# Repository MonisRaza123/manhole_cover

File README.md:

# MCMS (Manhole Cover Monitoring System)

## Problem Statement
Theft of manhole covers is a severe problem faced by our nation that has been left unaddressed for a long time.The repercussions of this thievery not only amount to material losses but also lead to loss of lives. This project proposes a solution to this problem by building a manhole cover monitoring system. Given that a sensor placed inside the manhole will not have reliable connection to the internet, we can directly send the sensor details using internet. This system will give the real-time status of the covers using a LoRa-based gateway to send the data to a cloud server keeping the authorities informed.

## Introduction and Motivation
Theft of manhole covers leads to accidents and deaths. At
first, this might seem like a very unlikely problem, but in
2004 Calcutta witnessed the theft of more than 10000
manhole covers over a period of two months. Thieves
steal these covers to sell them as scrap iron, the profit
made out of these acts is not much but the loss incurred
by society is much greater.
This type of theft is performed at locations experiencing
less traffic and spots which are not monitored with CCTV
cameras. These uncovered holes pose serious danger to
vehicles, especially two-wheelers which end in fatal crashes.
The pedestrians might be able to spot a big hole in daylight
but at night in darkness the chances of any mishappening
increase manifold.
Thus it becomes imperative to come up with a solution
to curb these acts of petty thievery leading to unfortunate
fatalities.

## Proposed Solution

The suggested model is represented in three sections:

1. **LoRa end-devices:** The end devices are composed of sensors capable of
monitoring the status of the cover on the manhole.
The microcontroller reading this sensor is integrated
with a LoRa transmitter.
1. **Integrating internet connectivity:** Signals from the nodes of a given region would be
received by a common LoRa-based gateway connected
to an internet access point.
1. **Cloud server and web interface:** Using the connectivity provided by the gateway, the
data is uploaded to a cloud-based server and displayed
on a web interface or sent to the municipal authorities.

## Block Diagram Representation
|||
|:--:|:--:|
|*Manhole(End Node)*|*Gateway*|

## Six Box Model
The following is the list of requirements for the proposed solution as per the 'Six box Model' for embedded systems:
- Input sensor to detect the status of the manhole cover.
- Wireless technology for transferring sensor information.
- Cloud server acting as the host and storage for the required data.
- Microcontroller to process and control the node and gateway.
- Power supply for the node and gateway.
- Output devices to access the monitoring of the manhole covers.

|1. INPUT- Flex sensor is used as the input sensor to detect the status of the manhole cover by bending at different angles. The resistance of the sensor changes with change in bending angle thereby facilitating the detection of the presence/absence of the cover.||
|:--|--:|
|2. COMMUNICAITON- LoRa communication is used as the preferred communication technology between the sensor node and the gateway because: i) Internet connectivity is not a viable option for the application. ii) LoRa is ideal for low bandwidth battery operated systems as it consumes minimal power ||
|3. HOST & STORAGE- Blynk IOT serves as the cloud service provider. It stores and hosts the cover status of multiple node devices centrally which can then be fetched remotely from anyplace and anytime.||
|4. POWER SUPPLY- The end nodes are powered by a battery and as such need to be charged periodically.The TP4056 is a complete constant-current/constant-voltage linear charger for single-cell lithium-ion batteries. Its SOP package and low external component count make the TP4056 ideally suited for portable applications. The gateway device is powered by a 5V DC adapter||

|<span style="font-weight:normal">5. MICROCONTROLLERS- ATMEGA168 is the microcontroller of choice for the end node as it consumes very less power and has just the right amount of features to cater to the needs of the end device. ESP32 is used as the microcontroller at the gateway as it requires internet connectivity serving as the internet access point for multiple end nodes. The communication between the end-nodes and gateway is done using Lora transceivers as stated earlier</span>|||
|:--|--|--:|

## Circuit Design

### Schematics
||
|:--:|
|*Schematic for End Node*|

||
|:--:|
|*Schematic for Master Node/Gateway*|

### Board Layouts
||
|:--:|
|*END NODE board layout*|

||
|:--:|
|*MASTER NODE board layout*|

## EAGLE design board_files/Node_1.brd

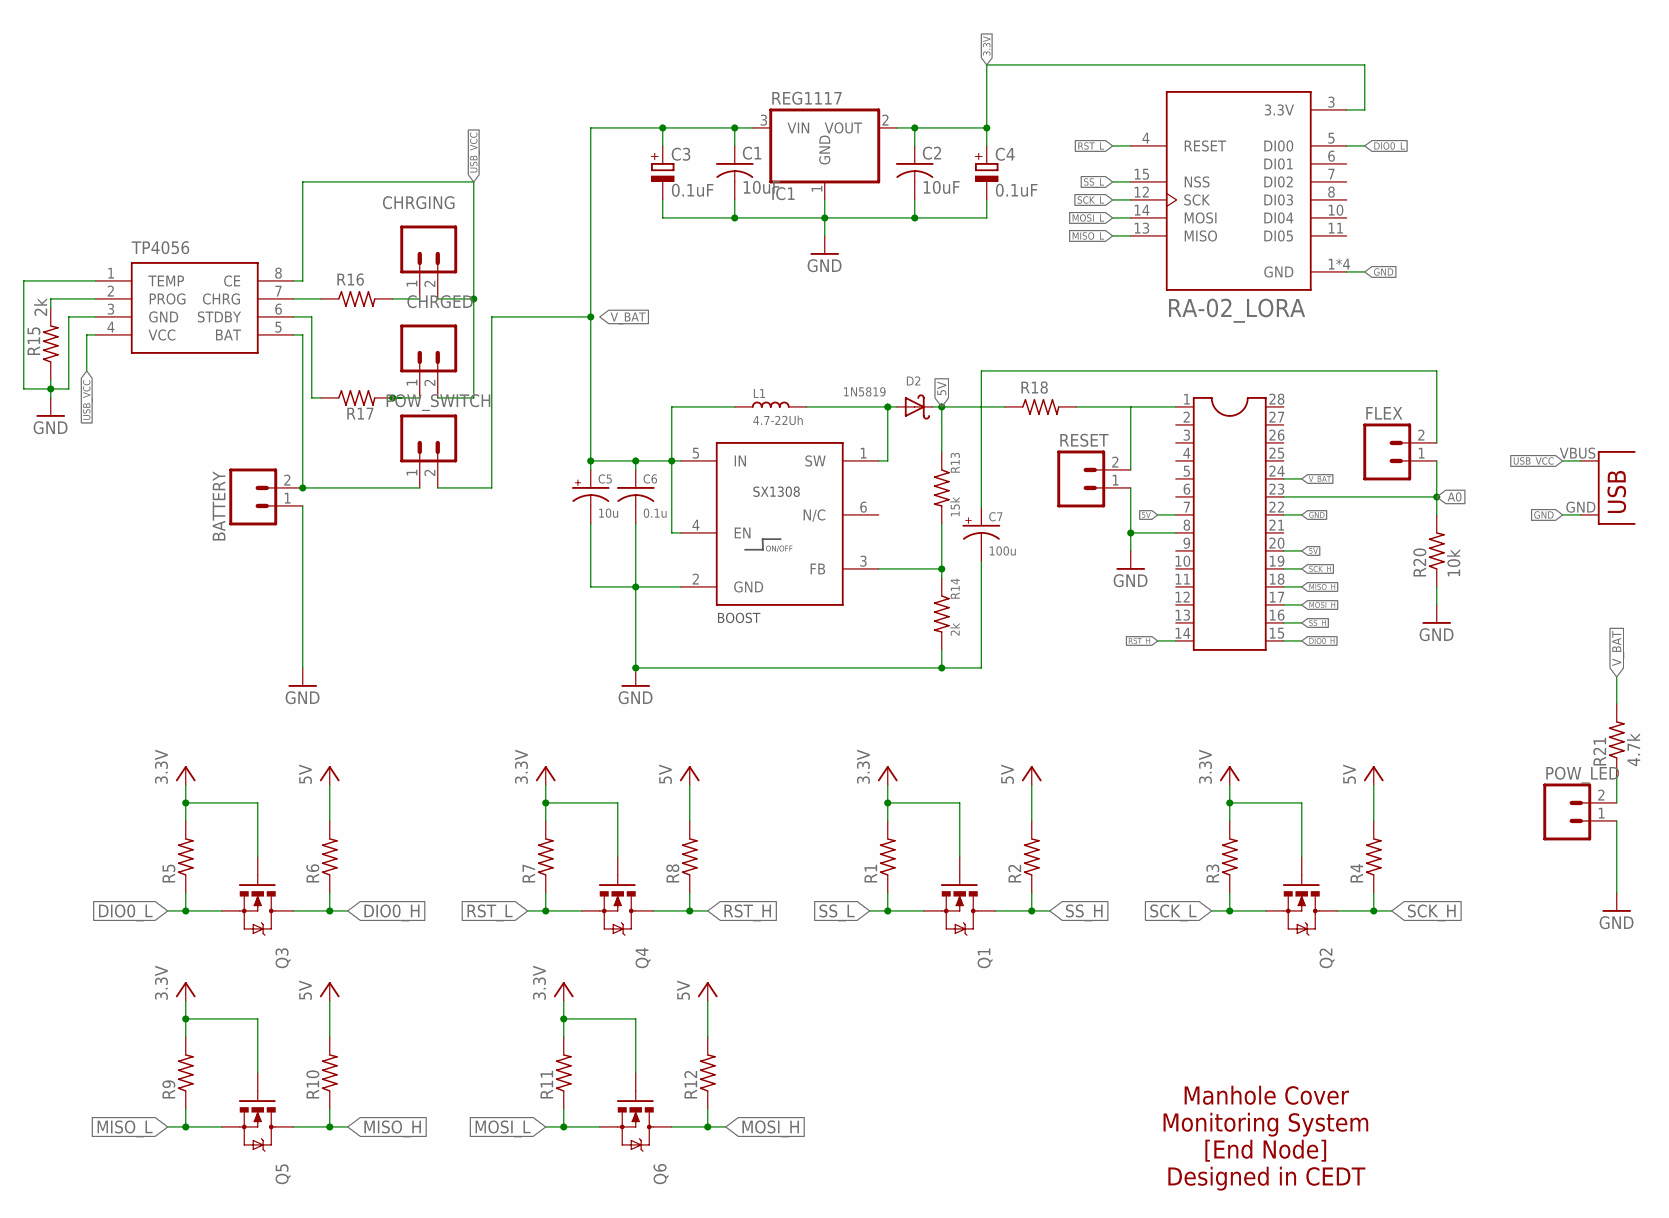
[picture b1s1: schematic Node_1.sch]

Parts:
ATMEGA168: DIL28-3
BATTERY: M02; 02P
BOOST: SX1308; SOT-23-6
C1, C2: 10uF; C0805
C3, C4: 0.1uF; CAPMP3528X210N
C5: 10u; B/3528-21R
C6: 0.1u; C0603
C7: 100u; C/6032-28R
CHRGED: M02; 02P
CHRGING: M02; 02P
D2: 1N5819; DO41-10
FLEX: M02; 02P
IC1: REG1117; SOT223
L1: 4.7-22Uh; INDUCTOR_INT2-3.5-D6.5XH8.0MM
POW_LED: M02; 02P
POW_SWITCH: M02; 02P
Q1, Q2, Q3, Q4, Q5, Q6: MOSFET-NCHANNELBSS138; SOT23
R1, R2, R3, R4, R5, R6, R7, R8, R9, R10, R11, R12: RESISTOR0805; R0805
R13: 15k; M0805
R14: 2k; M0805
R15: 2k; R0805
R16, R17: 470; 0207/7
R18: 10k; 0207/7
R20: 10k; 0207/10
R21: 4.7k; 0207/7
RESET: M02; 02P
TP4056: TP4056; SOP-8
U1: RA-02_LORA; MODULE_RA-02_LORA
U$1: USB(POWER)

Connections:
3.3V: C2.1, C4.1 (+), IC1.2 (VOUT), Q1.1 (G), Q2.1 (G), Q3.1 (G), Q4.1 (G), Q5.1 (G), Q6.1 (G), R1.2, R3.2, R5.2, R7.2, R9.2, R11.2, U1.3 (3.3V)
5V: ATMEGA168.7, ATMEGA168.20, C7.+, D2.C, FLEX.2, R2.2, R4.2, R6.2, R8.2, R10.2, R12.2, R13.1, R18.1
A0: ATMEGA168.23, FLEX.1, R20.2
BAT: BATTERY.2, POW_SWITCH.1, TP4056.5 (BAT)
DIO0_H: ATMEGA168.15, Q3.3 (D), R6.1
DIO0_L: Q3.2 (S), R5.1, U1.5 (DI00)
GND: ATMEGA168.8, ATMEGA168.22, BATTERY.1, BOOST.2 (GND), C1.2, C2.2, C3.2 (-), C4.2 (-), C5.-, C6.2, C7.-, IC1.1 (GND), POW_LED.1, R14.2, R15.1, R20.1, RESET.1, TP4056.1 (TEMP), TP4056.3 (GND), U1.1 (GND), U1.2 (GND), U1.9 (GND), U1.16 (GND), U$1.GND
MISO_H: ATMEGA168.18, Q5.3 (D), R10.1
MISO_L: Q5.2 (S), R9.1, U1.13 (MISO)
MOSI_H: ATMEGA168.17, Q6.3 (D), R12.1
MOSI_L: Q6.2 (S), R11.1, U1.14 (MOSI)
unnamed: BOOST.1 (SW), D2.A, L1.2
unnamed: R15.2, TP4056.2 (PROG)
unnamed: R16.1, TP4056.7 (CHRG)
unnamed: POW_LED.2, R21.1
unnamed: BOOST.3 (FB), R13.2, R14.1
unnamed: R17.1, TP4056.6 (STDBY)
unnamed: CHRGING.1, R16.2
unnamed: ATMEGA168.1, R18.2, RESET.2
unnamed: CHRGED.1, R17.2
RST_H: ATMEGA168.14, Q4.3 (D), R8.1
RST_L: Q4.2 (S), R7.1, U1.4 (RESET)
SCK_H: ATMEGA168.19, Q2.3 (D), R4.1
SCK_L: Q2.2 (S), R3.1, U1.12 (SCK)
SS_H: ATMEGA168.16, Q1.3 (D), R2.1
SS_L: Q1.2 (S), R1.1, U1.15 (NSS)
USB_VCC: CHRGED.2, CHRGING.2, TP4056.4 (VCC), TP4056.8 (CE), U$1.VBUS (VCC)
V_BAT: ATMEGA168.24, BOOST.4 (EN), BOOST.5 (IN), C1.1, C3.1 (+), C5.+, C6.1, IC1.3 (VIN), L1.1, POW_SWITCH.2, R21.2

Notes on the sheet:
Manhole Cover Monitoring System [End Node] Designed in CEDT

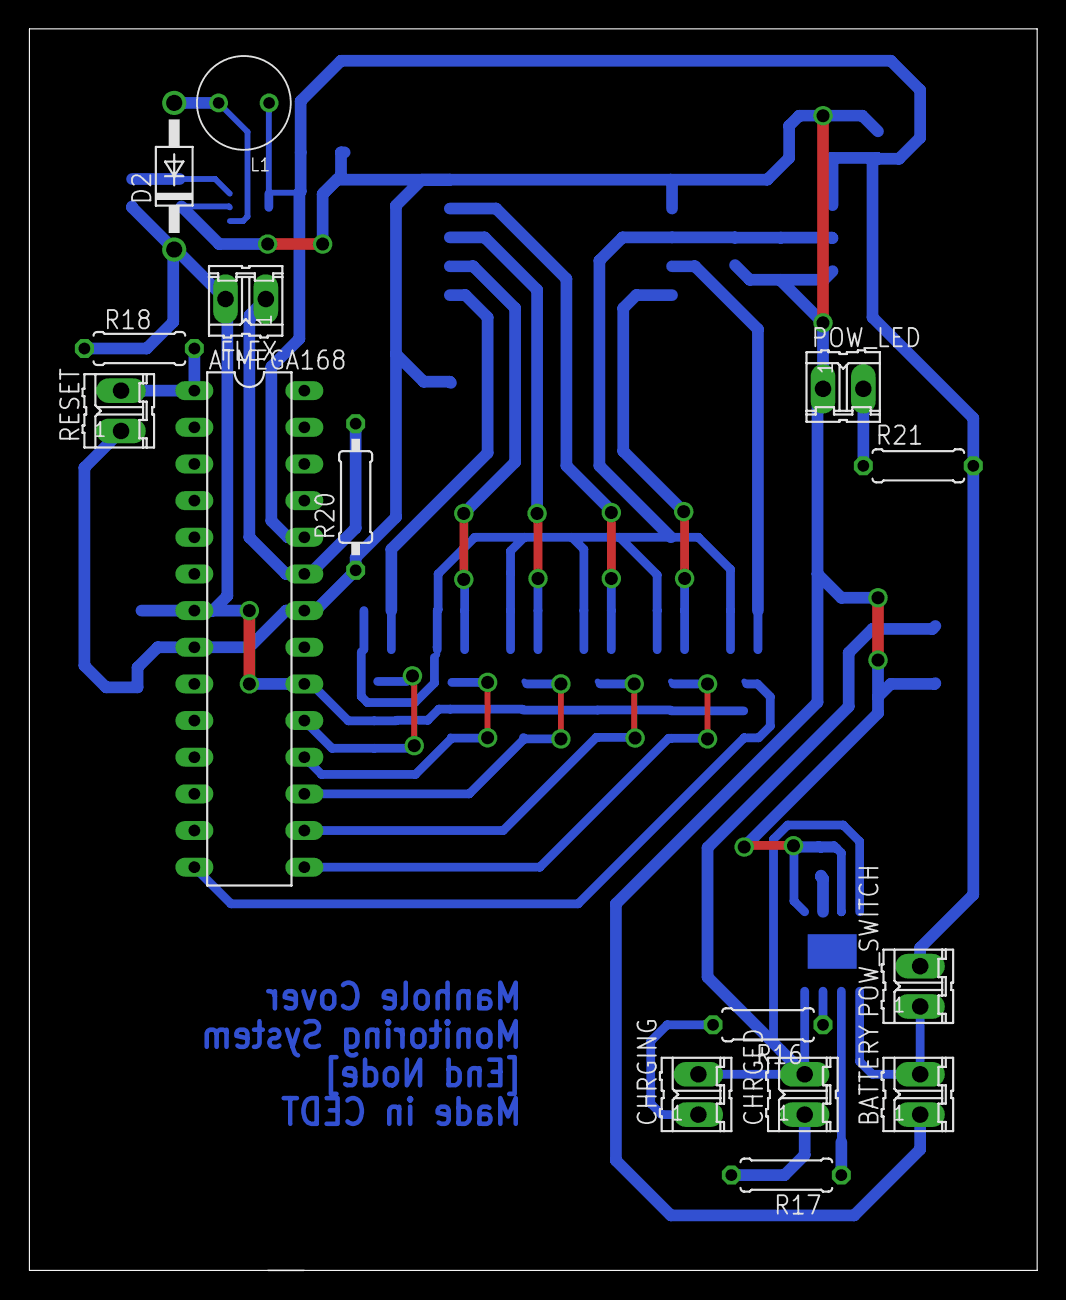
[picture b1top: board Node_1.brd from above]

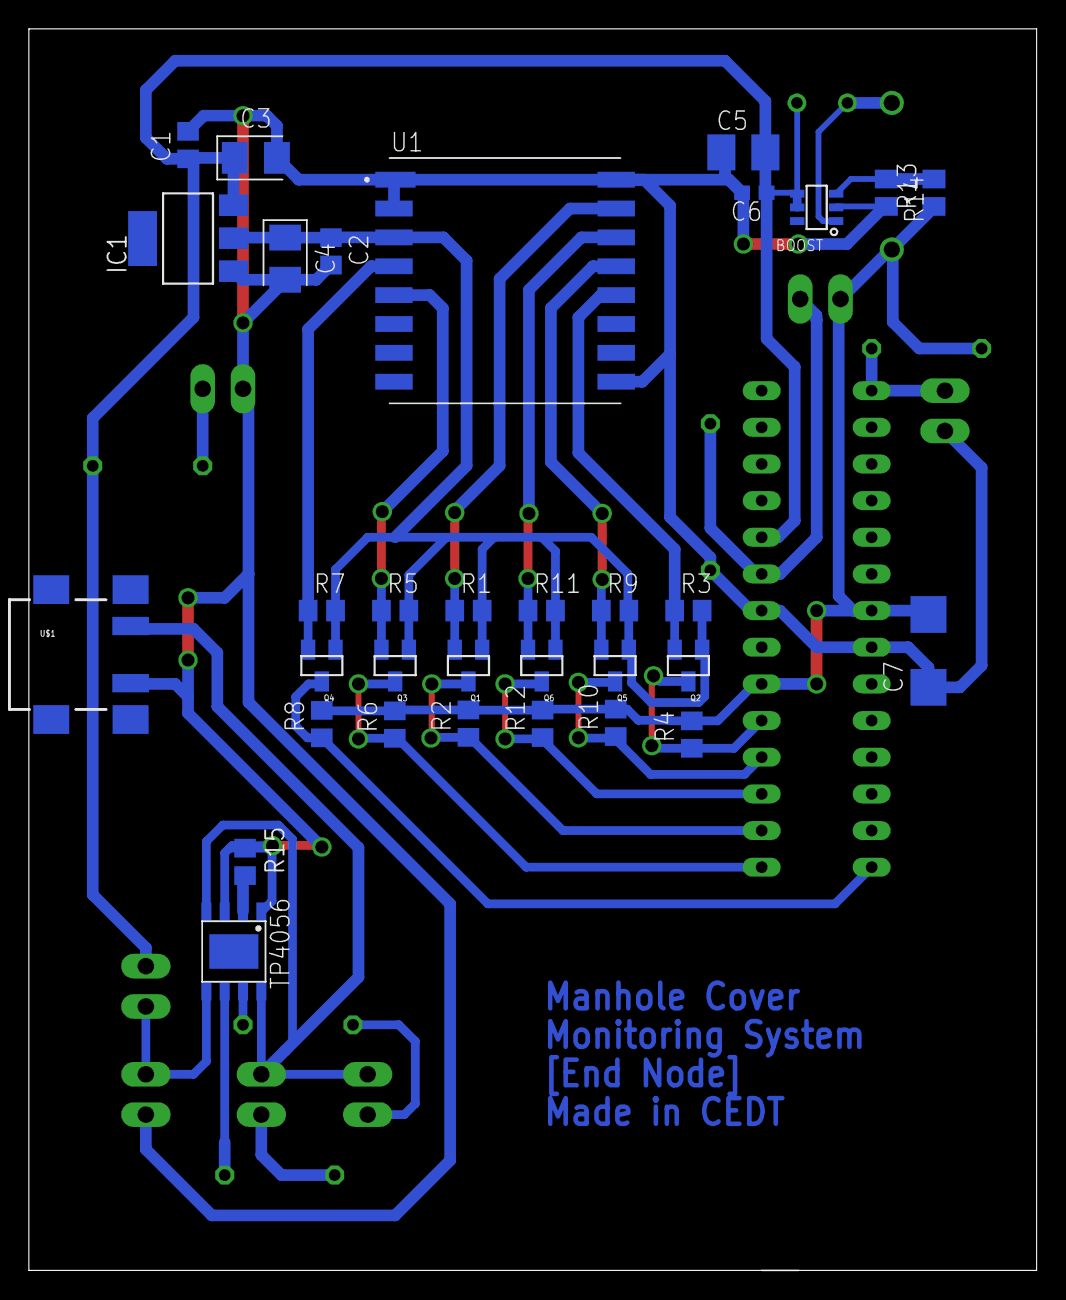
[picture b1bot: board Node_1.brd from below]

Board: 2 copper layers, 69.8 x 86.0 mm, 48 parts (33 on the bottom side), 28 nets.

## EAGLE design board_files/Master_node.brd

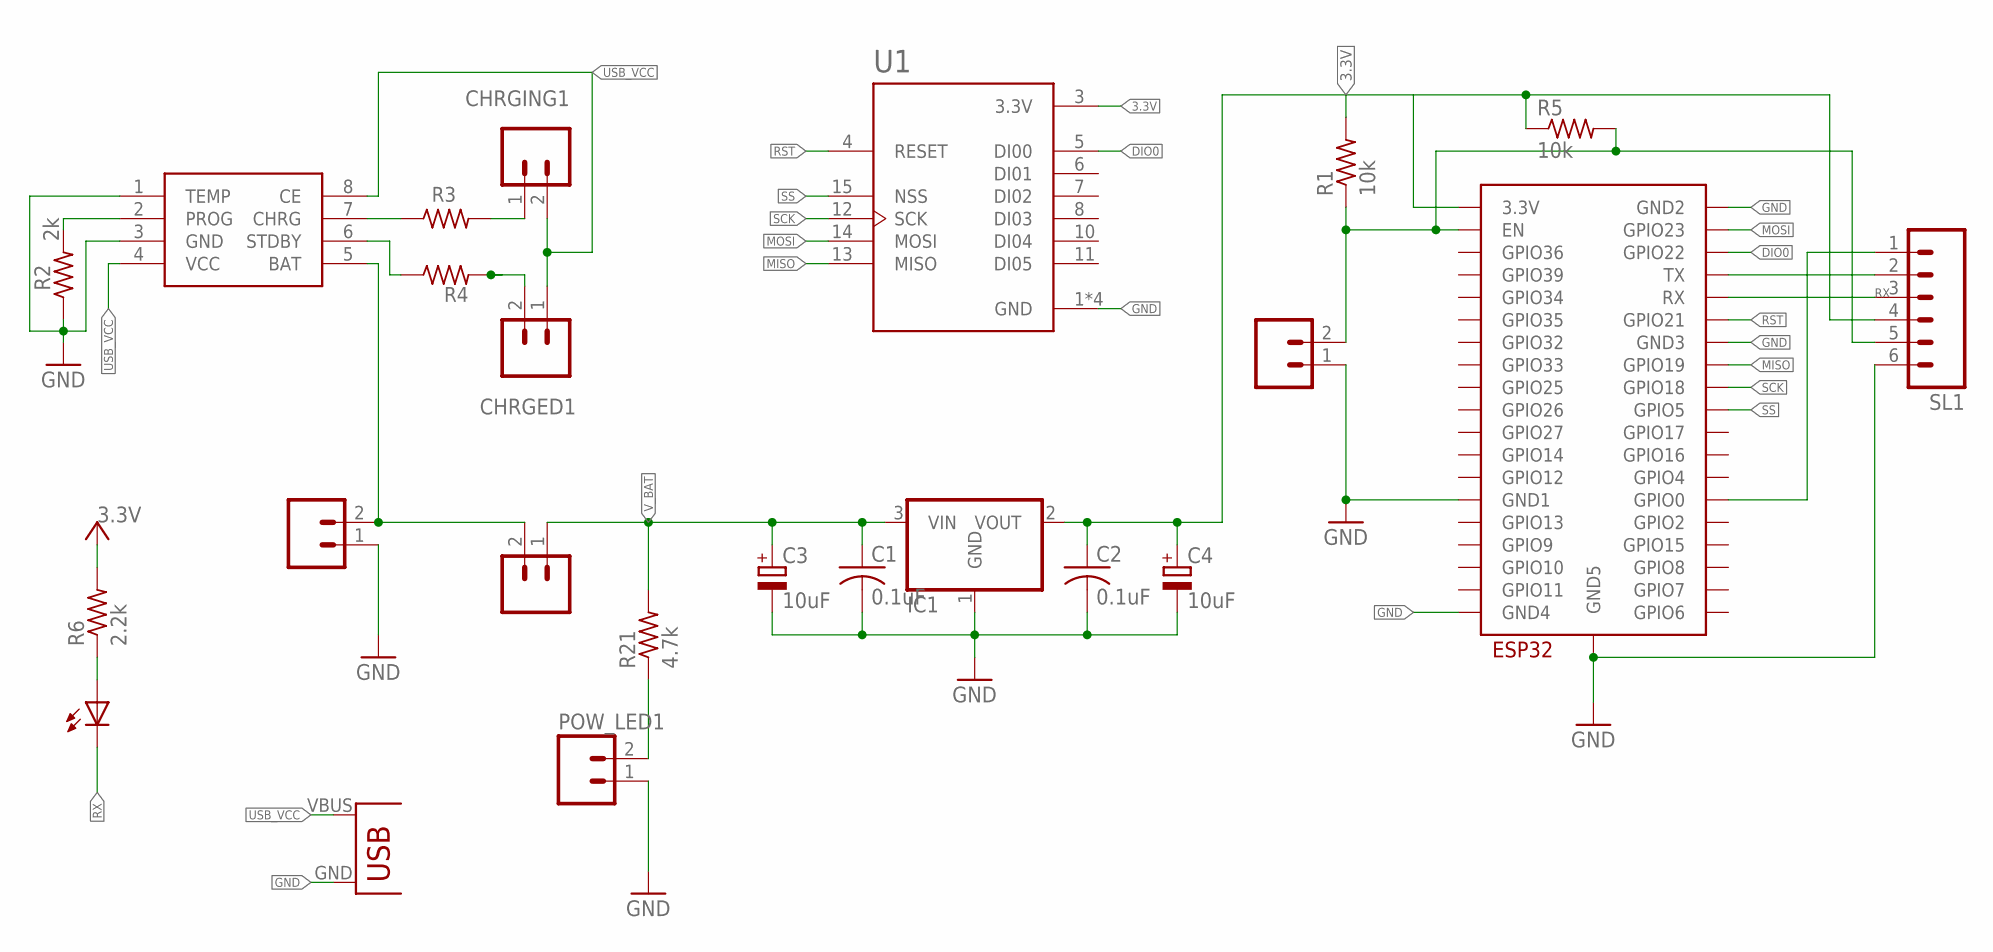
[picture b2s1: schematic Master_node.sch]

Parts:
BATTERY1: M02; 02P
C1, C2: 0.1uF; C0805
C3, C4: 10uF; CAPMP3528X210N
CHRGED1: M02; 02P
CHRGING1: M02; 02P
IC1: REG1117; SOT223
POW_LED1: M02; 02P
POW_SWITCH: M02; 02P
PROG_LED: LED0603; CHIPLED_0603
R1: 10k; 0207/7
R2: 2k; 0207/7
R3, R4: 470; 0207/7
R5: 10k; R0805
R6: 2.2k; R0805
R21: 4.7k; 0207/10
RESET: M02; 02P
SL1: M06; 06P
TP4056: TP4056; SOP-8
U1: RA-02_LORA; MODULE_RA-02_LORA
U$1: ESP32-WROOM
U$3: USB(POWER)

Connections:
3.3V: C2.1, C4.1 (+), IC1.2 (VOUT), R1.2, R5.1, R6.2, SL1.4, U1.3 (3.3V), U$1.3V3 (3.3V)
BAT: BATTERY1.2, POW_SWITCH.2, TP4056.5 (BAT)
DIO0: U1.5 (DI00), U$1.IO22 (GPIO22)
GND: BATTERY1.1, C1.2, C2.2, C3.2 (-), C4.2 (-), IC1.1 (GND), POW_LED1.1, R2.1, RESET.1, SL1.6, TP4056.1 (TEMP), TP4056.3 (GND), U1.1 (GND), U1.2 (GND), U1.9 (GND), U1.16 (GND), U$1.GND1, U$1.GND2, U$1.GND3, U$1.GND4, U$1.GND5, U$3.GND
MISO: U1.13 (MISO), U$1.IO19 (GPIO19)
MOSI: U1.14 (MOSI), U$1.IO23 (GPIO23)
unnamed: R1.1, R5.2, RESET.2, SL1.5, U$1.EN
unnamed: SL1.2, U$1.TX
unnamed: SL1.1, U$1.IO0 (GPIO0)
unnamed: R2.2, TP4056.2 (PROG)
unnamed: CHRGING1.1, R3.2
unnamed: PROG_LED.A, R6.1
unnamed: CHRGED1.2, R4.2
unnamed: R3.1, TP4056.7 (CHRG)
unnamed: R4.1, TP4056.6 (STDBY)
unnamed: POW_LED1.2, R21.1
RST: U1.4 (RESET), U$1.IO21 (GPIO21)
RX: PROG_LED.C, SL1.3, U$1.RX
SCK: U1.12 (SCK), U$1.IO18 (GPIO18)
SS: U1.15 (NSS), U$1.IO5 (GPIO5)
USB_VCC: CHRGED1.1, CHRGING1.2, TP4056.4 (VCC), TP4056.8 (CE), U$3.VBUS (VCC)
V_BAT: C1.1, C3.1 (+), IC1.3 (VIN), POW_SWITCH.1, R21.2

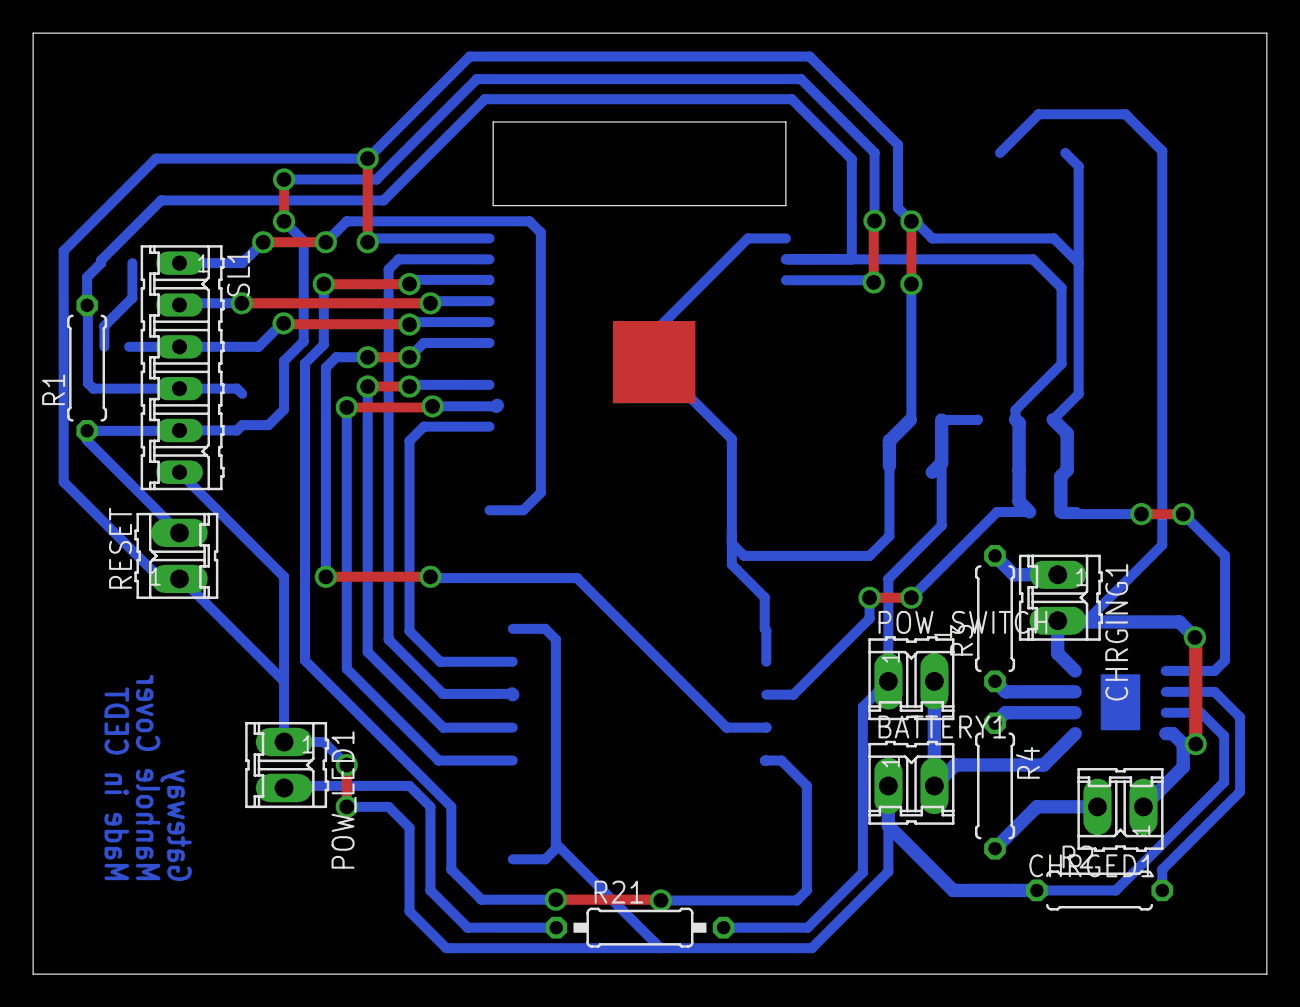
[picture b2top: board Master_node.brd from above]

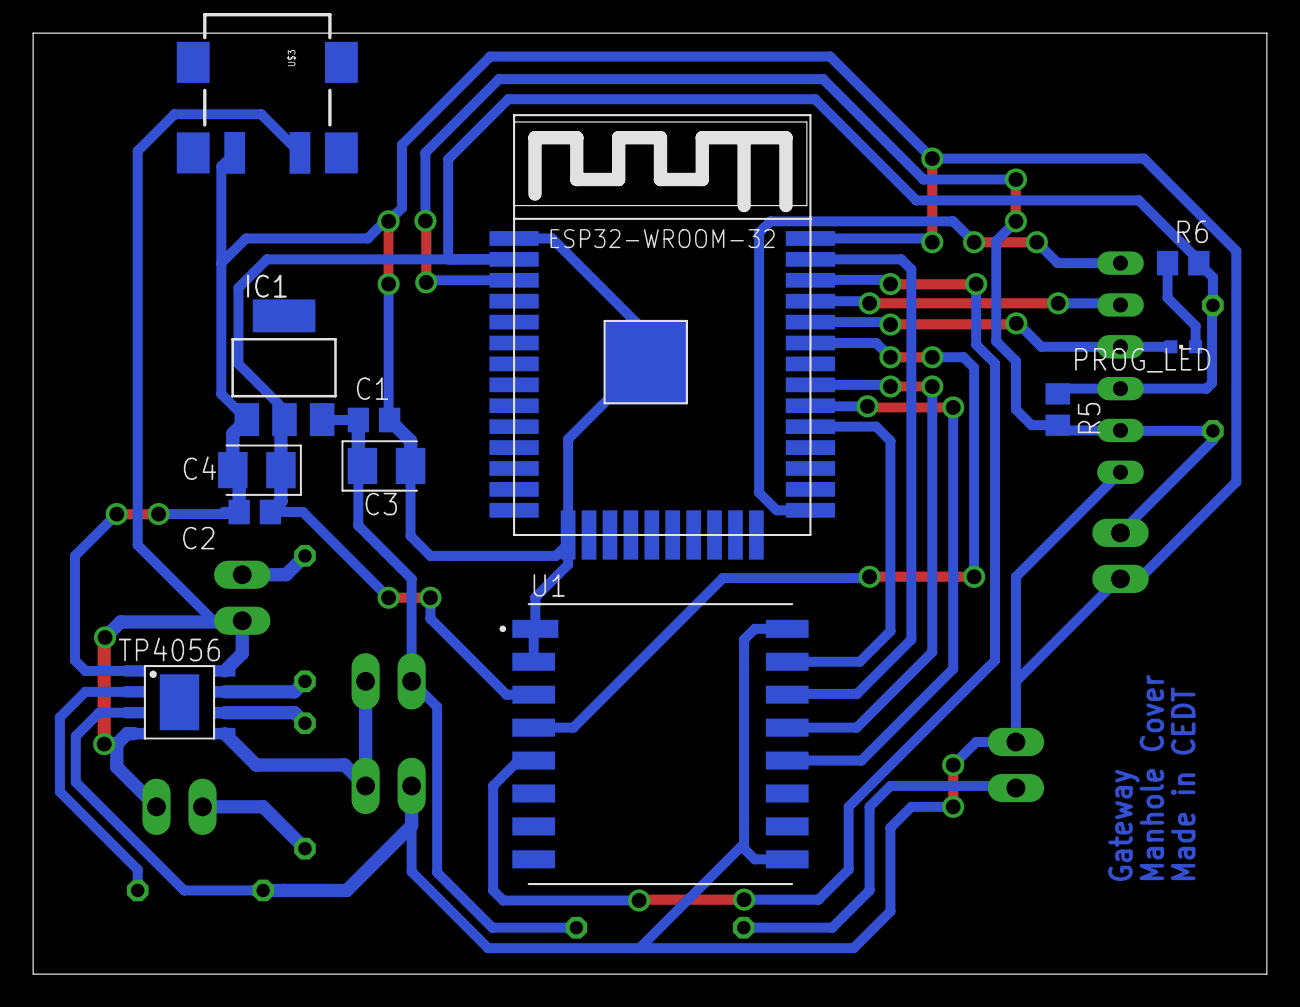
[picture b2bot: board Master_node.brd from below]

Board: 2 copper layers, 74.9 x 57.1 mm, 24 parts (12 on the bottom side), 22 nets.

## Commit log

2023-10-07 added img
2023-10-07 added blynk
